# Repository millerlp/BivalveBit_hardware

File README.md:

# BivalveBit hardware
 Heart rate and valve gape sensor wearable for oysters and mussels. 
 This hardware is described in the publication "Monitoring bivalve behavior and physiology in the laboratory and field using open-source tools" L.P. Miller (2022) *Integrative and Comparative Biology*
 
 [https://doi.org/10.1093/icb/icac046](https://doi.org/10.1093/icb/icac046)
 
 * Based around a ATmega4808 microcontroller
 * Designed to fit inside a nominal 3/4" schedule 40 PVC plumbing pipe (<18.5mm
 inside diameter) along with an 18650 size Lithium-Ion battery cell. 
 * Provides one I2C 4-pin port for communicating with a IR heart rate sensor
 * Provides one analog 4-pin port for communicating with an analog sensor such
 as the A1395 Hall effect sensor (with SLEEP pin on the 4th wire). 
 * Writes data to a standard microSD card

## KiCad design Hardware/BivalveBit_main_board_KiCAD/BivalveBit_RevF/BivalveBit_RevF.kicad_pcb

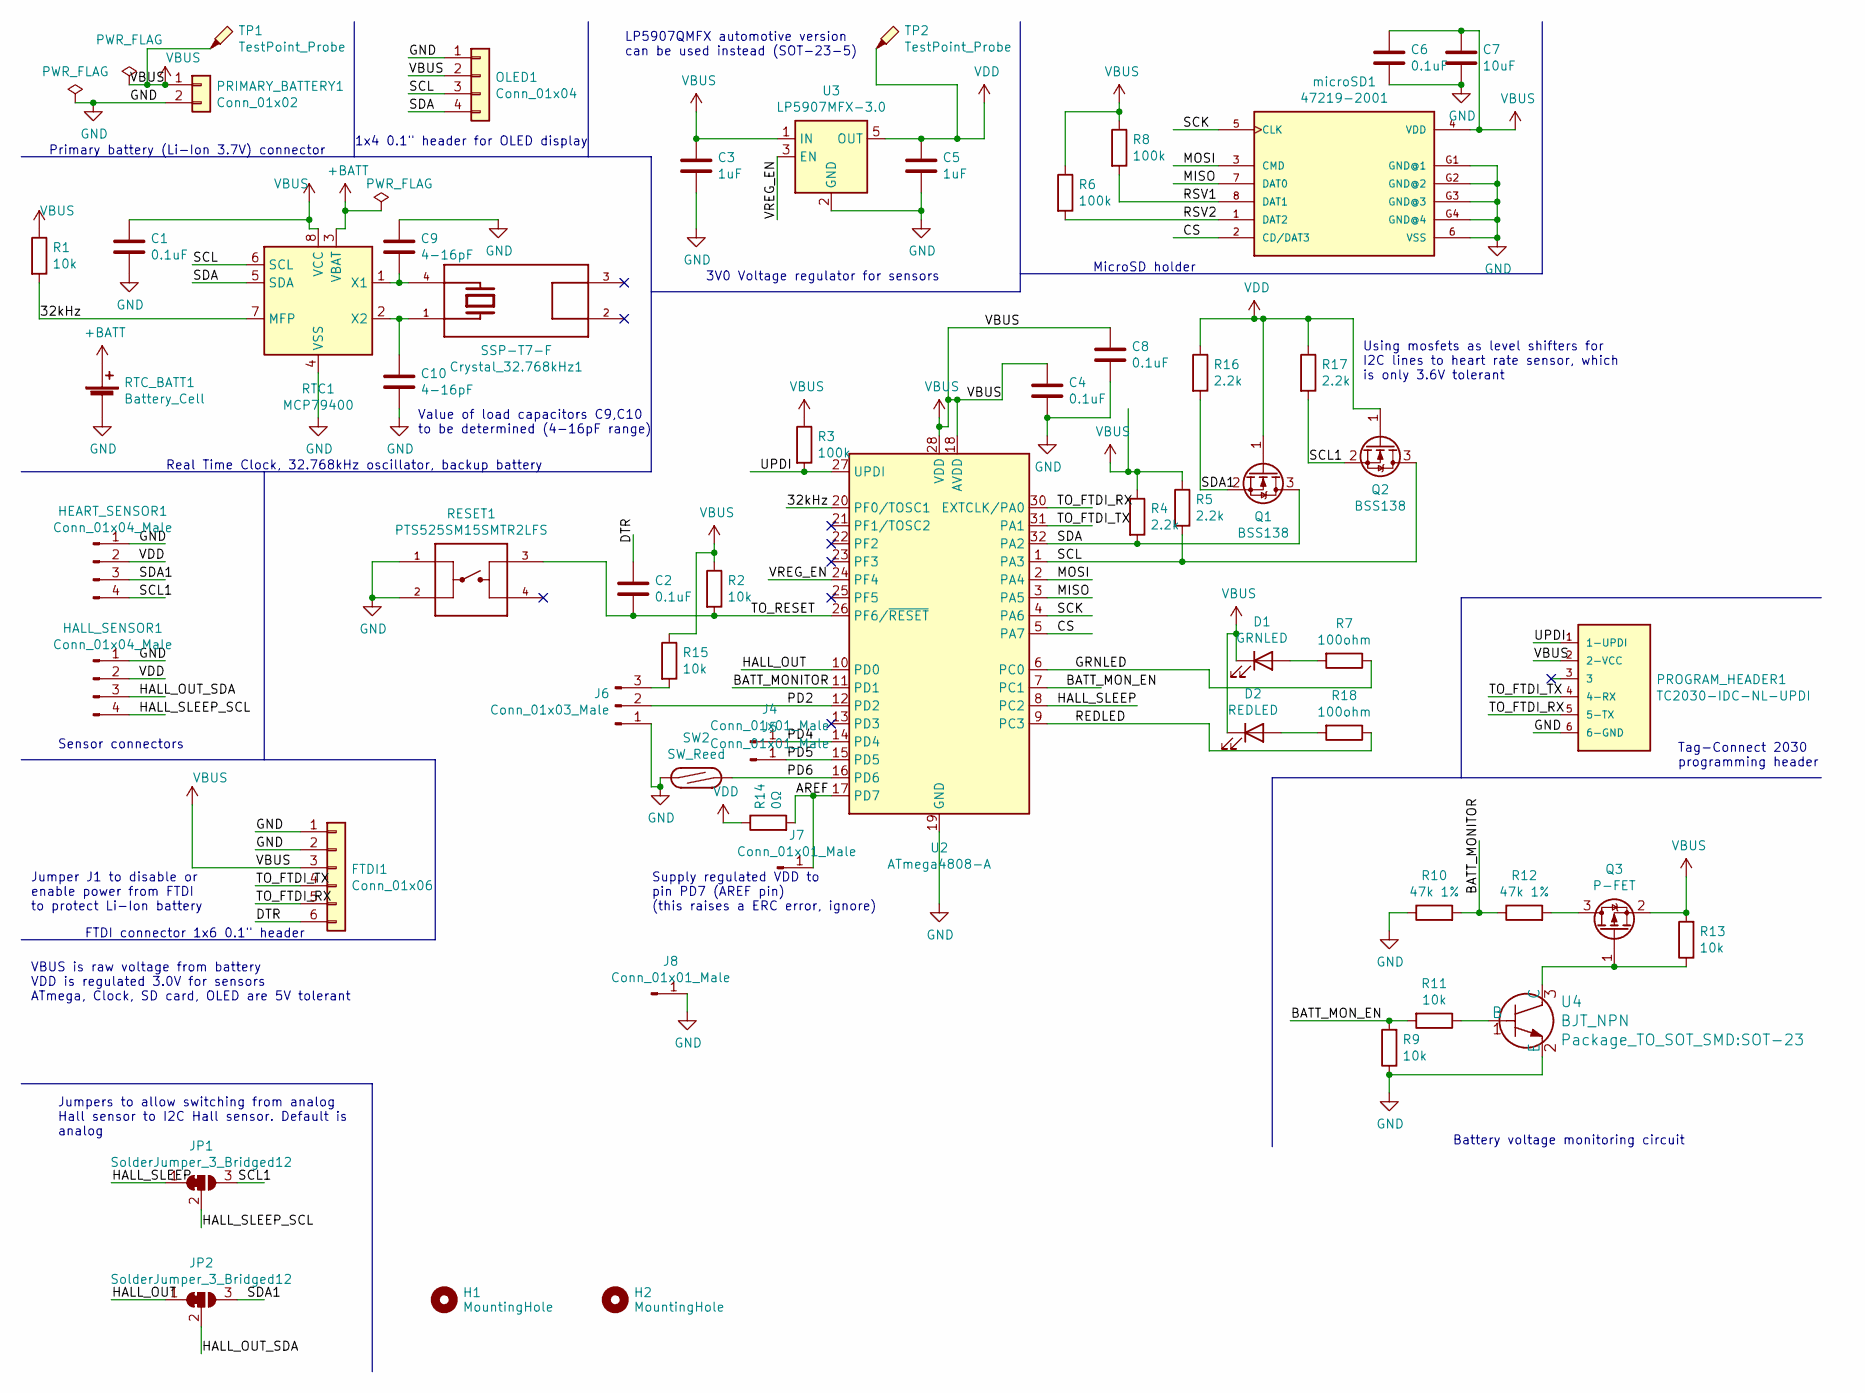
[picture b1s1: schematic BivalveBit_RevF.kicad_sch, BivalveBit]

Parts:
C1, C2, C4, C6, C8: 0.1uF; C_0603_1608Metric
C3, C5: 1uF; C_0603_1608Metric
C7: 10uF; C_0603_1608Metric
C9, C10: 4-16pF; C_0603_1608Metric
Crystal_32.768kHz1: SSP-T7-F; OSC_SSP-T7-F; PARTREV N/A
D1: GRNLED; LED_0805_2012Metric
D2: REDLED; LED_0805_2012Metric
FTDI1: Conn_01x06; PinSocket_1x06_P2.54mm_Horizontal
H1, H2: MountingHole; MountingHole_3.2mm_M3
HALL_SENSOR1: Conn_01x04_Male; JST_PH_B4B-PH-K_1x04_P2.00mm_Vertical
HEART_SENSOR1: Conn_01x04_Male; JST_PH_B4B-PH-K_1x04_P2.00mm_Vertical
J4, J5, J7, J8: Conn_01x01_Male; Pin_D1.0mm_L10.0mm
J6: Conn_01x03_Male; PinHeader_1x03_P2.54mm_Vertical
JP1, JP2: SolderJumper_3_Bridged12; SolderJumper-3_P1.3mm_Bridged12_RoundedPad1.0x1.5mm
OLED1: Conn_01x04; PinHeader_1x04_P2.54mm_Vertical
PRIMARY_BATTERY1: Conn_01x02; JST_PH_B2B-PH-K_1x02_P2.00mm_Vertical
PROGRAM_HEADER1: TC2030-IDC-NL-UPDI; Tag-Connect_TC2030-IDC-NL_2x03_P1.27mm_Vertical; PARTREV MS
Q1, Q2: BSS138; SOT-23
Q3: P-FET; SOT-23
R1, R2, R9, R11, R13, R15: 10k; R_0603_1608Metric
R3, R6, R8: 100k; R_0603_1608Metric
R4, R5, R16, R17: 2.2k; R_0603_1608Metric
R7, R18: 100ohm; R_0603_1608Metric
R10, R12: 47k 1%; R_0603_1608Metric
R14: 0Ω; R_0603_1608Metric
RESET1: PTS525SM15SMTR2LFS; SW_PTS525SM15SMTR2LFS; PARTREV NA
RTC1: MCP79400; MSOP-8_3x3mm_P0.65mm
RTC_BATT1: Battery_Cell; BatteryHolder_Keystone_3000_1x12mm
SW2: SW_Reed; SW_SPST_REED_CT10-XXXX-G1
TP1, TP2: TestPoint_Probe; TestPoint_THTPad_D1.0mm_Drill0.5mm
U2: ATmega4808-A; TQFP-32_7x7mm_P0.8mm
U3: LP5907MFX-3.0; SOT-23-5
U4: BJT_NPN; SOT-23
microSD1: 47219-2001; MOLEX_47219-2001; Digikey WM6698CT-ND

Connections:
+BATT: RTC1.3 (VBAT), RTC_BATT1.1 (+)
/32kHz: R1.2, RTC1.7 (MFP), U2.20 (PF0/TOSC1)
/AREF: J7.1, R14.2, U2.17 (PD7)
/BATT_MONITOR: R10.2, R12.1, U2.11 (PD1)
/BATT_MON_EN: R9.2, R11.2, U2.7 (PC1)
/CS: U2.5 (PA7), microSD1.2 (CD/DAT3)
/DTR: C2.1, FTDI1.6
/GRNLED: R7.1, U2.6 (PC0)
/HALL_OUT: JP2.1 (A), U2.10 (PD0)
/HALL_OUT_SDA: HALL_SENSOR1.3, JP2.2 (C)
/HALL_SLEEP: JP1.1 (A), U2.8 (PC2)
/HALL_SLEEP_SCL: HALL_SENSOR1.4, JP1.2 (C)
/MISO: U2.3 (PA5), microSD1.7 (DAT0)
/MOSI: U2.2 (PA4), microSD1.3 (CMD)
/PD2: J6.2, U2.12 (PD2)
/PD4: J4.1, U2.14 (PD4)
/PD5: J5.1, U2.15 (PD5)
/PD6: SW2.2, U2.16 (PD6)
/REDLED: R18.1, U2.9 (PC3)
/RSV1: R8.2, microSD1.8 (DAT1)
/RSV2: R6.2, microSD1.1 (DAT2)
/SCK: U2.4 (PA6), microSD1.5 (CLK)
/SCL: OLED1.3, Q2.3 (D), R5.2, RTC1.6 (SCL), U2.1 (PA3)
/SCL1: HEART_SENSOR1.4, JP1.3 (B), Q2.2 (S), R17.2
/SDA: OLED1.4, Q1.3 (D), R4.2, RTC1.5 (SDA), U2.32 (PA2)
/SDA1: HEART_SENSOR1.3, JP2.3 (B), Q1.2 (S), R16.2
/TO_FTDI_RX: FTDI1.5, PROGRAM_HEADER1.5 (5-TX), U2.30 (EXTCLK/PA0)
/TO_FTDI_TX: FTDI1.4, PROGRAM_HEADER1.4 (4-RX), U2.31 (PA1)
/TO_RESET: C2.2, R2.2, RESET1.3, U2.26 (PF6/~RESET)
/UPDI: PROGRAM_HEADER1.1 (1-UPDI), R3.2, U2.27 (UPDI)
/VREG_EN: U2.24 (PF4), U3.3 (EN)
GND: C1.2, C3.2, C4.2, C5.2, C6.2, C7.2, C8.2, C9.1, C10.2, FTDI1.1, FTDI1.2, HALL_SENSOR1.1, HEART_SENSOR1.1, J6.1, J8.1, OLED1.1, PRIMARY_BATTERY1.2, PROGRAM_HEADER1.6 (6-GND), R9.1, R10.1, RESET1.1, RESET1.2, RTC1.4 (VSS), RTC_BATT1.2 (-), SW2.1, U2.19 (GND), U2.29 (GND), U3.2 (GND), U4.2 (E), microSD1.6 (VSS), microSD1.G1 (GND@1), microSD1.G2 (GND@2), microSD1.G3 (GND@3), microSD1.G4 (GND@4)
unnamed: D1.2 (A), R7.2
unnamed: D2.2 (A), R18.2
unnamed: J6.3, R15.2
unnamed: Q3.3 (D), R12.2
unnamed: Q3.1 (G), R13.1, U4.3 (C)
unnamed: C9.2, Crystal_32.768kHz1.4, RTC1.1 (X1)
unnamed: C10.1, Crystal_32.768kHz1.1, RTC1.2 (X2)
unnamed: R11.1, U4.1 (B)
VBUS: C1.1, C3.1, C4.1, C6.1, C7.1, C8.1, D1.1 (K), D2.1 (K), FTDI1.3, OLED1.2, PRIMARY_BATTERY1.1, PROGRAM_HEADER1.2 (2-VCC), Q3.2 (S), R1.1, R2.1, R3.1, R4.1, R5.1, R6.1, R8.1, R13.2, R15.1, RTC1.8 (VCC), TP1.1, U2.18 (AVDD), U2.28 (VDD), U3.1 (IN), microSD1.4 (VDD)
VDD: C5.1, HALL_SENSOR1.2, HEART_SENSOR1.2, Q1.1 (G), Q2.1 (G), R14.1, R16.1, R17.1, TP2.1, U3.5 (OUT)

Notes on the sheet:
Primary battery (Li-Ion 3.7V) connector
Battery voltage monitoring circuit
Using mosfets as level shifters for I2C lines to heart rate sensor, which is only 3.6V tolerant
Jumpers to allow switching from analog Hall sensor to I2C Hall sensor. Default is analog
FTDI connector 1x6 0.1" header
Sensor connectors
1x4 0.1" header for OLED display
Real Time Clock, 32.768kHz oscillator, backup battery
Supply regulated VDD to pin PD7 (AREF pin) (this raises a ERC error, ignore)
Value of load capacitors C9,C10 to be determined (4-16pF range)
LP5907QMFX automotive version can be used instead (SOT-23-5)
Jumper J1 to disable or enable power from FTDI to protect Li-Ion battery
3V0 Voltage regulator for sensors
VBUS is raw voltage from battery VDD is regulated 3.0V for sensors ATmega, Clock, SD card, OLED are 5V tolerant
MicroSD holder
Tag-Connect 2030 programming header

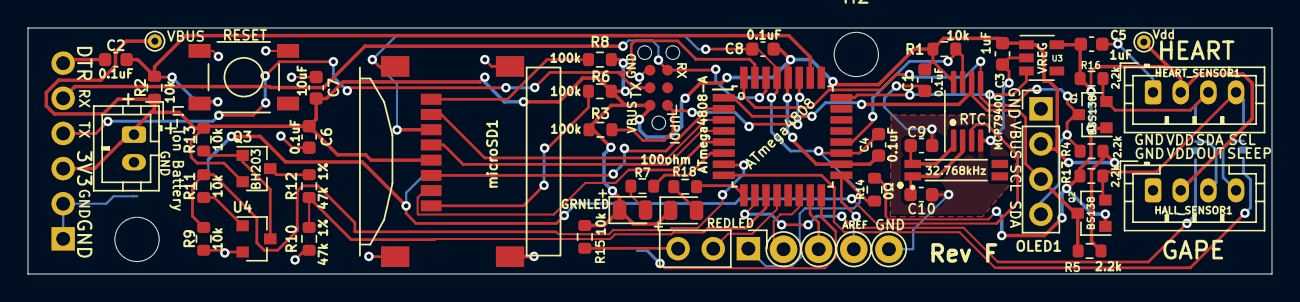
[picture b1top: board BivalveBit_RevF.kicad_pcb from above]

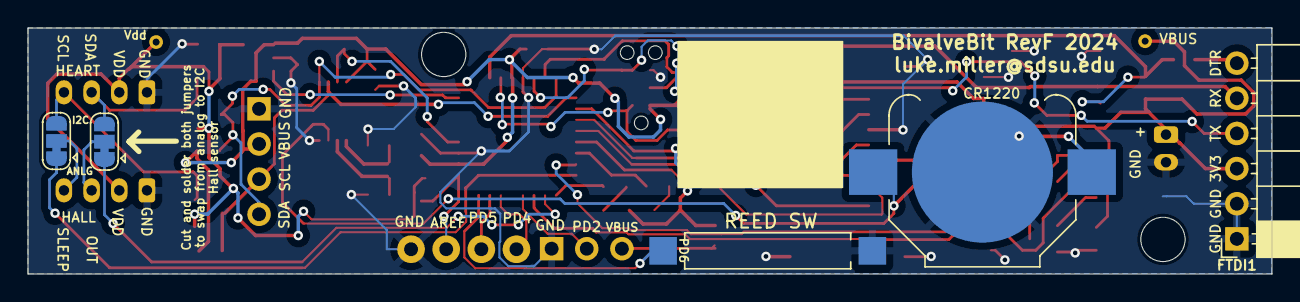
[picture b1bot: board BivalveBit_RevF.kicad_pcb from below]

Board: 2 copper layers, 89.9 x 17.8 mm, 59 parts (5 on the bottom side), 42 nets.

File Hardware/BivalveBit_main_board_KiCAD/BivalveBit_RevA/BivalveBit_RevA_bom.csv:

Id,Designator,Package,Quantity,Designation,Supplier and ref
1,RTC_BATT1,BatteryHolder_Keystone_3000_1x12mm_small_pad,1,Battery_Cell,
2,J1,PinHeader_1x02_P2.54mm_Vertical,1,Conn_01x02_Male,
3,"R17,R16,R5,R4",R_0603_1608Metric,4,2.2k,
4,U4,SOT-23,1,FMMT619TA,
5,U3,SOT-23-5,1,LP5907,
6,U2,TQFP-32_7x7mm_P0.8mm,1,ATmega4808,
7,U1,TSSOP-14_4.4x5mm_P0.65mm,1,PCF8523TS,
8,SW2,SW_SPST_REED_CT10-XXXX-G1,1,SW_Reed,
9,RESET,SW_PTS525SM15SMTR2LFS,1,PTS525SM15SMTR2LFS,
10,"R15,R14,R13,R11,R9,R2,R1",R_0603_1608Metric,7,10k,
11,"R12,R10",R_0603_1608Metric,2,47k 1%,
12,"R8,R6,R3",R_0603_1608Metric,3,100k,
13,R7,R_0603_1608Metric,1,100ohm,
14,Q3,SOT-23,1,IRLML5203,
15,"Q2,Q1",SOT-23,2,BSS138,
16,PROGRAM_HEADER1,Tag-Connect_TC2030-IDC-NL_2x03_P1.27mm_Vertical,1,TC2030-IDC-NL-UPDI,
17,PRIMARY_BATTERY1,JST_PH_B2B-PH-K_1x02_P2.00mm_Vertical,1,Conn_01x02,
18,OLED1,PinHeader_1x04_P2.54mm_Vertical,1,Conn_01x04,
19,microSD,MOLEX_47219-2001,1,47219-2001,
20,"J7,J5,J4,J3,J2,J8",Pin_D1.0mm_L10.0mm,6,Conn_01x01_Male,
21,J6,PinHeader_1x03_P2.54mm_Vertical,1,Conn_01x03_Male,
22,"HEART_SENSOR1,HALL_SENSOR1",JST_PH_B4B-PH-K_1x04_P2.00mm_Vertical,2,Conn_01x04_Male,
23,FTDI,PinSocket_1x06_P2.54mm_Horizontal,1,Conn_01x06,
24,D1,LED_0805_2012Metric,1,LED,
25,32.768kHz,OSC_SSP-T7-F,1,SSP-T7-F,
26,"C8,C6,C4,C2,C1",C_0603_1608Metric,5,0.1uF,
27,C7,C_0603_1608Metric,1,10uF,
28,"C5,C3",C_0603_1608Metric,2,1uF,

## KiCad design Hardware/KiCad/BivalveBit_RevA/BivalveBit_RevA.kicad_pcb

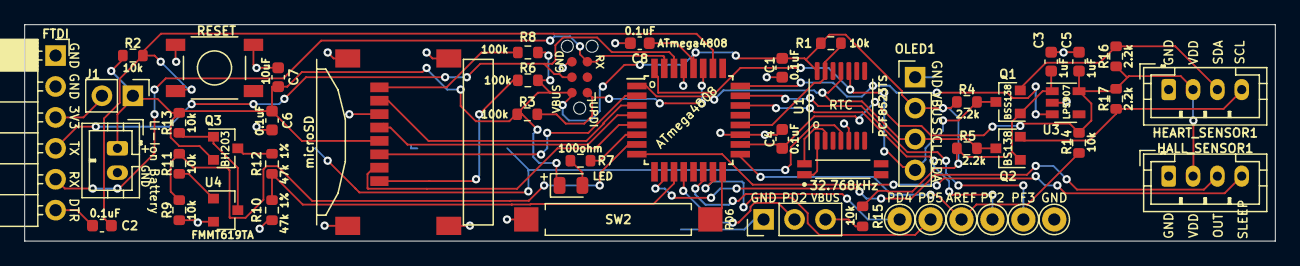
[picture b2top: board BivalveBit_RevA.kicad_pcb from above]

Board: 2 copper layers, 102.7 x 17.8 mm, 52 parts (1 on the bottom side), 41 nets.

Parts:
32.768kHz: SSP-T7-F; OSC_SSP-T7-F
C1, C2, C4, C6, C8: 0.1uF; C_0603_1608Metric
C3, C5: 1uF; C_0603_1608Metric
C7: 10uF; C_0603_1608Metric
D1: LED; LED_0805_2012Metric
FTDI: Conn_01x06; PinSocket_1x06_P2.54mm_Horizontal
HALL_SENSOR1: Conn_01x04_Male; JST_PH_B4B-PH-K_1x04_P2.00mm_Vertical
HEART_SENSOR1: Conn_01x04_Male; JST_PH_B4B-PH-K_1x04_P2.00mm_Vertical
J1: Conn_01x02_Male; PinHeader_1x02_P2.54mm_Vertical
J2, J3, J4, J5, J7, J8: Conn_01x01_Male; Pin_D1.0mm_L10.0mm
J6: Conn_01x03_Male; PinHeader_1x03_P2.54mm_Vertical
OLED1: Conn_01x04; PinHeader_1x04_P2.54mm_Vertical
PRIMARY_BATTERY1: Conn_01x02; JST_PH_B2B-PH-K_1x02_P2.00mm_Vertical
PROGRAM_HEADER1: TC2030-IDC-NL-UPDI; Tag-Connect_TC2030-IDC-NL_2x03_P1.27mm_Vertical
Q1, Q2: BSS138; SOT-23
Q3: IRLML5203 or BH203,215; SOT-23
R1, R2, R9, R11, R13, R14, R15: 10k; R_0603_1608Metric
R3, R6, R8: 100k; R_0603_1608Metric
R4, R5, R16, R17: 2.2k; R_0603_1608Metric
R7: 100ohm; R_0603_1608Metric
R10, R12: 47k 1%; R_0603_1608Metric
RESET: PTS525SM15SMTR2LFS; SW_PTS525SM15SMTR2LFS
RTC_BATT1: Battery_Cell; BatteryHolder_Keystone_3000_1x12mm_small_pad
SW2: SW_Reed; SW_SPST_REED_CT10-XXXX-G1
U1: PCF8523TS; TSSOP-14_4.4x5mm_P0.65mm
U2: ATmega4808; TQFP-32_7x7mm_P0.8mm
U3: LP5907; SOT-23-5
U4: FMMT619TA; SOT-23
microSD: 47219-2001; MOLEX_47219-2001

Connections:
+BATT: RTC_BATT1.1, U1.4
/3V3_FTDI: FTDI.3, J1.2
/32kHz: R1.2, U1.13, U2.20
/AREF: J7.1, R14.2, U2.17
/BATT_MONITOR: R10.2, R12.1, U2.11
/BATT_MON_EN: R9.2, R11.2, U2.7
/CS: U2.5, microSD.2
/DTR: C2.1, FTDI.6
/HALL_OUT: HALL_SENSOR1.3, U2.10
/HALL_SLEEP: HALL_SENSOR1.4, U2.8
/LED: R7.1, U2.6
/MISO: U2.3, microSD.7
/MOSI: U2.2, microSD.3
/PD2: J6.2, U2.12
/PD4: J4.1, U2.14
/PD5: J5.1, U2.15
/PD6: SW2.2, U2.16
/PF2: J2.1, U2.22
/PF3: J3.1, U2.23
/RSV1: R8.2, microSD.8
/RSV2: R6.2, microSD.1
/SCK: U2.4, microSD.5
/SCL: OLED1.3, Q2.3, R5.2, U1.11, U2.1
/SCL1: HEART_SENSOR1.4, Q2.2, R17.2
/SDA: OLED1.4, Q1.3, R4.2, U1.10, U2.32
/SDA1: HEART_SENSOR1.3, Q1.2, R16.2
/TO_FTDI_RX: FTDI.5, PROGRAM_HEADER1.5, U2.31
/TO_FTDI_TX: FTDI.4, PROGRAM_HEADER1.4, U2.30
/TO_RESET: C2.2, R2.2, RESET.3, U2.26
/UPDI: PROGRAM_HEADER1.1, R3.2, U2.27
/VREG_EN: U2.24, U3.3
GND: C1.2, C3.2, C4.2, C5.2, C6.2, C7.2, C8.2, FTDI.1, FTDI.2, HALL_SENSOR1.1, HEART_SENSOR1.1, J6.1, J8.1, OLED1.1, PRIMARY_BATTERY1.2, PROGRAM_HEADER1.6, R9.1, R10.1, RESET.1, RESET.2, RTC_BATT1.2, SW2.1, U1.5, U2.19, U2.29, U3.2, U4.2, microSD.6, microSD.G1, microSD.G2, microSD.G3, microSD.G4
unnamed: 32.768kHz.1, U1.1
unnamed: 32.768kHz.4, U1.2
unnamed: D1.2, R7.2
unnamed: J6.3, R15.2
unnamed: Q3.1, R13.1, U4.3
unnamed: Q3.3, R12.2
unnamed: R11.1, U4.1
VBUS: C1.1, C3.1, C6.1, C7.1, C8.1, D1.1, J1.1, OLED1.2, PRIMARY_BATTERY1.1, PROGRAM_HEADER1.2, Q1.1, Q2.1, Q3.2, R1.1, R2.1, R3.1, R4.1, R5.1, R6.1, R8.1, R13.2, R15.1, U1.14, U2.28, U3.1, microSD.4
VDD: C4.1, C5.1, HALL_SENSOR1.2, HEART_SENSOR1.2, R14.1, R16.1, R17.1, U2.18, U3.5

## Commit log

2021-01-29 Ignore Notes directory
2021-01-30 Ignore datasheets directory
2021-10-08 Gerber stuff
2022-01-19 Example board picture
2022-02-28 Moving hardware files around
2022-05-18 Saving some layout images
2022-06-08 Transferring design to KiCad
2022-12-06 Backups
2023-01-19 Thickening traces, no layout changes
2023-07-13 Re-saving in KiCad 7
2024-03-04 Some backups
2024-03-04 Creating Rev F
    Added mounting holes, thickened traces
2024-03-04 Few minor label changes
2025-05-29 Moving images around
2025-05-29 Moving parts list here
2025-05-29 Update the ignore
2025-05-29 Moving pictures around
